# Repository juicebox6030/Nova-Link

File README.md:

# NOVA-LINK

NOVA-LINK is an open wireless protocol and firmware SDK for live event applications
such as lighting, audio control, and synchronization. The intended system uses an
ESP32-S3 plugin host and a TI CC1352R radio co-processor.

The repository currently provides a **portable C99 implementation of the protocol
and application core**, with tests and an in-memory simulation. Native SPI host
and slave adapters provide portable asynchronous ownership boundaries; physical
SPI/GPIO drivers and over-the-air operation still require implementation and
validation. Dual-band
redundancy and sub-5 ms delivery are design targets, not measured capabilities.

## Build and try it without hardware

Requires CMake 3.16+ and a C99 compiler. Python 3 enables inspection and RF-budget tests;
Doxygen enables API documentation. The library has no third-party dependencies.

```sh
cmake -S . -B build -DCMAKE_BUILD_TYPE=Debug
cmake --build build --parallel
ctest --test-dir build --output-on-failure
./build/nova-sim
./build/nova-plugin-sim
./build/nova-plugin-fault-sim
./build/nova-spi-pair-sim
./build/nova-spi-duplex-sim
./build/nova-config-manifest examples/plugins.ini
./build/nova-inspect frame 'AA 06 03 AF FE 00 AA FF'
./build/dmx_loopback
```

The simulation sends 300 counter messages through two plugin hosts, framed
transport, radio queues, and simulated RF delivery. Every message arrives twice,
as a model of redundant bands; exactly one copy reaches the receiving plugin.
The 8-bit sequence counter wraps during the run. Time is logical, so this does
not measure RF latency or physical throughput.

For memory and undefined-behavior checks on a toolchain with sanitizer runtimes:

```sh
cmake -S . -B build/sanitized -DCMAKE_BUILD_TYPE=Debug -DNOVA_ENABLE_SANITIZERS=ON
cmake --build build/sanitized --parallel
ctest --test-dir build/sanitized --output-on-failure
```

Build just the library for integration:

```sh
cmake -S . -B build/core -DNOVA_BUILD_TESTS=OFF -DNOVA_BUILD_TOOLS=OFF -DNOVA_BUILD_EXTENDED=OFF
cmake --build build/core
```

Use `add_subdirectory()` and link `NovaLink::nova_link`, or install the SDK with
`cmake --install build/core --prefix <sdk-directory>` and use
`find_package(NovaLink 0.1 CONFIG REQUIRED)`. See the
[development guide](docs/Development.md) for plugin and embedded integration.
The independent DMX library is installed as `NovaLink::nova_dmx`.
Link `NovaLink::nova_plugins` for the included counter, Multiverse-model,
radio-link transport, asynchronous native SPI backend, logger, configuration and
capture plugins, or select their individual targets.
The base initializes with `nl_host_init_plugins()`; an unordered manifest starts
providers before consumers, and `nl_host_poll()` polls input then ticks plugins.
See [the compiled plugin guide](plugins/README.md) for the common module API.

Generate a standalone plugin starter with
`python3 tools/new_plugin.py my-plugin --kind application --output build/my_plugin`.
The generated CMake project uses the installed SDK and includes a lifecycle smoke
test and a reusable [plugin conformance suite](docs/Plugin_Conformance.md).
The [development guide](docs/Development.md) explains how to build it.
Link `NovaLink::nova_plugin_conformance` from plugin tests to check the common
lifecycle contract; reports distinguish exercised cases from unsupported optional
capabilities. `NovaLink::nova_fault_backend` provides selectable deterministic
delay, disconnect and congestion scenarios for transport tests. These developer
targets are separate from `NovaLink::nova_plugins` and the ESP-IDF component.
The [configuration service](docs/Plugin_Configuration.md) and offline
`nova-config-manifest` example compose installed plugins from bounded INI text.
Run `nova-plugin-fault-sim` for deterministic delayed transfers, disconnects,
congestion and explicit restart; see its
[scenario guide](docs/Transport_Fault_Simulation.md).
The [hardware preparation guide](docs/Hardware_Preparation.md) uses the documented
ESP32-S3, TI CC1352R and City Theatrical 5911 reference. Its capture service stages
raw observations in the existing JSONL schema; board I/O and real Multiverse RF
decoding still require implementation and measurements. Both documented vendor
compile projects build with pinned SDK/toolchain baselines; see the guide for
their artifacts and deployment records.
The [native SPI backend](docs/SPI_Backend.md) connects the radio-link provider to
a caller-supplied asynchronous driver. Its completion outcomes and receipt tokens
are local adapter metadata; the existing wire format defines no physical PUSH
acknowledgment or empty/error response.
`NovaLink::nova_spi_virtual` is an explicit developer dependency that connects
the actual host backend and slave helper using native serialized frames. Run
`nova-spi-pair-sim` for the counter/Multiverse-model pair under logical transfer
delays and injected faults. See the [SPI simulation guide](docs/SPI_Backend.md).
Run `nova-spi-duplex-sim` for simultaneous two-way 512-slot DMX using production
plugin ticks, exact frame checks, congestion, outage recovery and silence expiry.
The virtual driver is excluded from the production plugin aggregate and
ESP-IDF component; its software outcomes do not establish physical timing or
Multiverse interoperability.

## Implemented core

- Explicit DataFragment serialization, field/length validation, and golden vectors.
- Command framing and incremental parsing across arbitrary byte boundaries.
- Per-origin/per-zone duplicate and stale-packet rejection, including sequence wrap.
- Exclusive or shared read-only zone claims; globally accessible metadata zone 0.
- Static plugin registration with generation handles, startup rollback, shutdown,
  payload send/receive, periodic hooks, and guarded structured logging callbacks.
- Named modules with declarative claims, provider dependencies, transactional
  manifest startup, and dependency/ownership checks during shutdown.
- Lifecycle-managed transport and logging providers using the same plugin API.
- Configuration service with bounded, schema-validated INI buffers and typed values.
- Bounded TX/RX queues with in-process backpressure, retry-safe deduplication,
  and optional latest-state coalescing per stream.
- Clock-driven zone rounds, optional metadata slots, and bounded burst extensions.
- PUSH/PULL command handling with transactional PULL receipts, offline JSON
  inspection, an RF airtime calculator, and a counter plugin.
- Native complete-frame slave adapter and lifecycle-managed asynchronous SPI
  driver service, with immutable transfers and shutdown ownership checks.
- CMake installation, an ESP-IDF component definition, and Doxygen documentation.

All core storage is fixed or caller-owned. The library does not allocate memory,
create threads, read configuration files, or access a network or device. Its APIs
require serialized calls from the application's event loop. Zone checks provide
cooperative access control for trusted compiled plugins; they are not a memory
sandbox.

## Protocol

Eight logical zones are available: zone 0 for metadata, zones 1–7 for plugin data.
Plugins own application payload encoding. The implemented fragment is:

```text
[origin:3 | zone:3 | BURST:1 | MGMT_LISTEN:1][sequence:8][0..100 payload bytes]
```

The maximum serialized fragment is 102 bytes. Larger messages require an
application-defined fragmentation/reassembly format; the core returns an error
instead of truncating or inventing such a format.

The software transport envelope is `[0xAA][LEN][COMMAND][DATA]`, where `LEN`
includes the command. This makes the existing command list and variable payloads
unambiguous in software. Its compatibility with a future board adapter still
needs validation. The [protocol decisions](docs/Protocol_Decisions.md) explain
conflicting earlier notes, sequence limits, and unspecified commands.

## DMX and Multiverse work

The portable DMX library encodes level frames and parses validated UART
BREAK/MARK/byte events. The [Multiverse bench plan](docs/Multiverse_2_4GHz.md)
describes direct CC1352R interoperability work. The capture analyzer accepts
existing JSONL observations:

```sh
python3 tools/analyze_rf_capture.py examples/rf_capture.simulated.jsonl
```

The [Multiverse software emulator](docs/Multiverse_Emulator.md) now models both
TX and RX: chunked full/delta updates, asynchronous completion/retry ownership,
atomic receive reconstruction, duplicate/loss handling, and resynchronization.
Generate and replay a synthetic capture through the same C receive engine:

```sh
./build/nova-multiverse-sim --seed 42 --loss-percent 20 \
  --capture build/multiverse.synthetic.jsonl
python3 tools/replay_multiverse.py build/multiverse.synthetic.jsonl \
  --end-us 3130200 --summary-only
```

The installed `NovaLink::nova_multiverse` library exposes normalized DMX state
and adapter ownership APIs. Its synthetic test codec is excluded from SDK
installation. Actual Multiverse RF reception, decoding, transmission, and fixture
operation remain unimplemented and unverified; the RF format needs real evidence.
The analyzer also supports `--compare-stimuli baseline channel_1_32` to inspect
candidate byte differences in labeled captures without claiming channel decoding.

The installed `NovaLink::nova_multiverse_plugin` connects that engine to the
common host/module lifecycle. It segments a 512-channel frame into native NLM1
application payloads, retries queue pressure, and delivers complete RX frames
atomically. `nova-plugin-sim` runs it alongside counter, transport and logger
plugins with injected loss/corruption and final recovery. NLM1 is a documented
NOVA-LINK application format; real Multiverse RF still needs captures and hardware.

## Proposed compact hardware

The [DMX dongle and USB-C power barrel design](docs/hardware/DMX_Dongle_and_Power_Barrel.md)
describes a TI-only, fixture-adjacent isolated-DMX dongle requiring 2.4 GHz and
US 915 MHz RF hardware, with a 10–30 second
backup target, wired RDM/wireless management and DMX/RDM firmware-update provisions,
with USB-C power only, plus inline powerCON,
TRUE1 and NEMA 5-15 barrel variants with a rotating, positively locking USB-C
center section. It includes an [illustrated design](docs/hardware/dmx-hardware-concept.html)
and [candidate BOM](docs/hardware/dmx-hardware-bom.csv). The
[manufacturer review package](hardware/compact-dmx/README.md) includes editable
Rev B CAD/STEP comparison geometry, dimensioned drawings and a partial DMX schematic.
The Rev C prototype captures power/buffer/cutoff/service circuitry and 2 MiB SPI
staging flash with USB power only, plus source-backed MCU support and a dual-band
frontend with a dual-feed antenna prototype and manual termination assembled OFF.
Three separate captured projects pass KiCad ERC. All37 physical MCU/RF/DMX parts
have footprint assignments:36 source-backed and one provisional switch. Cold-cap startup,
antenna tuning/coupling, complete PCB design, mechanism details, fixture fit and qualification remain open;
this is not released build-to-print hardware.
The [fixture reference manifest](docs/hardware/fixture-reference-manifest.md)
records retrieved manufacturer CAD for four fixtures across ETC, CHAUVET and GLP,
with connector-clearance measurements and physical fit still to be verified.

## Extended protocol prototype

The [extended prototype](experimental/extended/README.md) preserves the separate
implementation with CRC-8 link frames, metadata discovery, segmentation, INI
configuration, Python codecs, and a multi-node RF simulator. The default build
tests it alongside the SDK; use `-DNOVA_BUILD_EXTENDED=OFF` to omit it.

Its `[AA][CMD][LEN][DATA][CRC8]` transport differs from the SDK's
`[AA][LEN][CMD][DATA]`. Both libraries export overlapping `nl_*` symbols and
must be used in separate programs. The extended API is not part of the installed
SDK. Neither transport is an established physical-radio interoperability format.

## Project layout

| Directory | Purpose |
|---|---|
| `include/nova_link/` | Public C API |
| `src/` | Portable protocol, host, and radio core |
| `plugins/` | Compiled application, transport, logger and configuration plugins |
| `support/` | Reusable plugin conformance harness for developer tests |
| `examples/` | Native and Multiverse-model simulations and DMX loopback |
| `tools/` | Plugin starters, offline inspection, RF budgets/capture comparisons, and synthetic replay |
| `tests/` | Unit, integration, CLI, and installed-SDK checks |
| `platform/` | Board integration contracts and ESP-IDF component |
| `config/` | CMake package configuration |
| `experimental/extended/` | Separate extended API, simulator, codecs, and vectors |
| `docs/` | Architecture, development guide, decisions, and roadmap |

Generate the public API reference with `cmake --build build --target docs` when
Doxygen is installed. Output is `build/api-docs/html/index.html`.
The `docs-extended` target generates the prototype reference in
`experimental/extended/build/doxygen/html/index.html`.

The CI workflow template is [config/ci.github-actions.yml](config/ci.github-actions.yml).
Copy it to `.github/workflows/ci.yml` to enable GitHub Actions; publishing that
path requires GitHub authentication with the `workflow` scope. Local build and
CTest checks do not require it.

The [development roadmap](docs/Development_Roadmap.md) separates completed software
from remaining protocol decisions and board work. The [validation record](docs/Validation.md)
documents software checks, Opus 5.5 High checkpoint reviews, and RF assumptions.

## License and credits

[GPL-3.0](LICENSE). Designed by [Brent Scoggins](https://github.com/Juicebox6030),
[Luminary Technology and Productions](https://LuminaryTechnology.productions).
AI-assisted development.

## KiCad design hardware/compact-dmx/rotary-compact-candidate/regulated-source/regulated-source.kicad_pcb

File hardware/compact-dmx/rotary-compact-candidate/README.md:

# Compact rotary collar — bounded Phase 0 disposition

**Stop: the unchanged IRM-10-5 → long FPC → TPS25810 source path does not establish4.75V at a1.5A receptacle.** A completeØ60–64 mechanism is therefore not claimed or exported. This is the authorized Phase0 infeasibility branch, not a replacement production design. Only this new folder changes; integrated25, baseline CAD/BOM/docs and cell-protection remain untouched.

Four actual primary PDFs were fetched and read: MeanWell IRM-10 specification2025-08-08; TI TPS25810 SLVSCR1C July2017; Minco2019 Flex Design Guide; AllFlex Minimum Bend Radius Considerations. Manufacturer electrical/dimensional pages were rendered and inspected. Existing exact GCT A6 drawing/A3 specification and USB-C R2.4 primary cache were read. `sources.json` records paths/URLs/hashes; no distributor evidence, supplier contact or new tooling.

## Decisive electrical screen

IRM-10-5 is a fixed5V/2A/10W module,45.7×25.4×21.5 nominal, each dimensional tolerance±0.5. Its±2.5% output tolerance already includes setup,line and load regulation: **4.875V minimum at25°C**. Do not subtract line/load twice, assume output adjustment, or turn the3W model into a1.5A supply. Maximum ripple is200mVpp; it is not quietly treated as zero or a guaranteed symmetric±100mV waveform. Temperature coefficient±0.03%/°C applies0–50°C; no full-temperature low-voltage bound beyond it is inferred. Source:IRM-10 pp2–3.

TPS25810 power-path resistance maxima are37mΩ at25°C,46mΩ to85°C,55mΩ to125°C, specified at3A; using those resistances at1.5A is a conservative engineering DC screen, not a new characterization claim. In1.5A mode CHG=high,CHG_HI=low; short-circuit threshold1.58–1.82A. ItsCC controller advertises current, **does not regulate low VBUS upward**. TI §9 explicitly requires4.75–5.5V at the receptacle. Source§6.5,§8 and§9. A captive-cable source's different load-line allowance in USB-C R2.4§4.8.1.2 cannot be applied to this receptacle.

`screen.py` evaluates0.8/1.0/1.1m and35/70µm copper at20/80°C, with two8mm traces. Copperρ20=1.75e−8Ωm andα=.00393/°C are engineering allocations; actual finished foil resistance must be guaranteed by the flex supplier. Corner assumes width7.8mm, copper−10%,20mΩ total board/solder/termination resistance, plus55mΩ controller. The termination allocation **excludes mated connector/cable contact resistance**, so the test is not pessimistically charging cable loss to the source pin.

All12 combinations miss4.75V. Even an optimistic1m/70µm/8mm at20°C, no copper thinning, **zero termination loss**, and25°C controller37mΩ yields **4.72575V**. The explicit hot/process model is in `screen.json`; flex heating and individual drops are listed. This is enough to reject a guarantee without relying on unspecified cold, ripple or module thermal behavior.

At125°C-controller resistance, only28.33mΩ remains for the entire flex loop even with zero termination loss. At1m/80°C/8mm, that requires **190.8µm actual copper**; with the20mΩ termination allocation it requires **648.8µm**. These are mathematical break-even values before ripple, not proposed dynamic-flex constructions. Increasing trace thickness until the equation passes is not a credible compact clockspring design.

GCT USB4125-GF-A provides3A collectiveVBUS component capability. Its initial40mΩ/contact and post-test50mΩ/contact specifications concern a mated connector; equal sharing across twoVBUS/twoGND contacts would add a40/50mΩ total loop respectively, but current sharing must be established and this loss was not required to prove the source failure. Temperature rise testing is component-specific, not complete barrel qualification.

### One bounded compensation direction, not silently implemented

Retain the stationary isolated10W module but add **local regulated5.10V±1% on the rotating side, before TPS25810**, so the regulator sees and corrects flex drop. This requires a new selected buck-boost/power-stage design; no part is invented, installed or captured here. With55mΩ controller plus20mΩ downstream paths, conditional port minimum is4.9365V, leaving186.5mV for ripple/transient/additional uncertainties. This stays within5.5V at no load under the assumed regulation, but overshoot and fault limits need actual component evidence.

At90% allocated efficiency and15mW auxiliary output, input power is8.517W. With the worst screened70µm/1.1m hot FPC and the module's conditional50°C low4.8375V, solve the constant-power input quadratic: **1.843A**, regulator input **4.622V**. This is below2A nominal rating but is not startup/short-circuit/thermal qualification. A part must demonstrate the required efficiency, input range, current limit, output regulation, soft-start and protection before this can be adopted. Thick copper, extra regulator footprint and heat all affect compactness; no complete64mm packing is claimed.

IRM-10's horizontal free-air curves give full power only through50°C and≥100VAC; output derates at higher temperature and below100VAC. It is75% around60°C, which cannot supply an8.517W regulator input.77% module efficiency is typical, not worst;8.517W at77% implies about2.54W module heat, plus converter/FPC/controller heat in the enclosure. A provisional design study could restrict module-local ambient to0–40°C and line≥100VAC, but **external barrel ambient and enclosed full-load performance remain undeclared/unqualified**. All three mains end families stay stationary with PE; their connector voltage/current/endcap/approval limits remain baseline gates. This direction does not authorize a source architecture change.

### Separate connector compliance objection

The exact GCT is six-contact/power-only: no D+/D− contacts. USB-C R2.4§4.8.1.1 requires a non-data receptacle charger to advertise≥1.5A and short D+/D− below200Ω for legacy charging compatibility. TPS25810+this connector cannot implement that physical connection. This does not negate the connector's current rating or the sidecar sink candidate, but **a compliant general charger claim is unsupported**. Parent must resolve product/connector requirements before source release; no alternative family search is performed.

## Mechanical feasibility boundaries — not a motion validation

Baseline remains stationaryØ48×142,Ø84×26 collar,Ø64 index ring, approximatelyØ80 source-board allocation. Mains, PE and AC/DC module do not rotate. A64mm outer shell with1.5mm wall permits outer dynamic radius30.5; allow inner dynamic radius25 for core/bearing/barrier clearance. Proposed study construction:20mm axial width, single RA copper layer, two8mm traces separated1mm and1.5mm edge margins. A0.16mm **allocated** total flex thickness is not a supplier-approved70µm stack. No plated features/stiffener ends in the active bend; tangential clamped terminations and independent axial faces are mandatory. Minco calls for single-layer dynamic flex and avoiding plated bend conductors; neither guide certifies our bend cycle life. AllFlex static thickness-ratio examples are not promoted to dynamic endurance ratings.

A simple six-turn Archimedean spiral at radii25..30.5 has **1046.165mm** neutral length and0.9167mm pitch. `spiral-diagnostic.csv` samples181angles,−90..+90, with finite0.16mm thickness: radial interturn gap stays≥0.72mm. **But its length changes−43.589/+43.589mm** when turn count changes±0.25 with both radii fixed. It is not an inextensible cable solution, and its end tangent also changes. If length is instead held constant by letting the outer radius move, the−90° state needs **R32.912mm**, already outside the30.5mm dynamic boundary; it also breaks the fixed rotating termination radius. This falsifies that tempting procedural shortcut, **not every possible elastic clockspring**.

Accordingly no181-position collision PASS, constant-length mechanism, working hard stops or shrink STEP is fabricated. A true candidate needs an inextensible elastic strip/path model with both tangent clamps, contact/friction/finite pitch and guides, then supplier validation. Arbitrary wire torsion is rejected; no twist-life source supports it.

Axial-end USB is better than the old radialØ80 envelope, but not yet a complete pack. For example, place a1mm board with inner faceR26, topR27. GCT nominal3.16height and8.94tangential width gives outer corner radius `sqrt(30.16²+4.47²)=30.489mm`. With source drawing general±.25, use3.41height/9.19width: **R30.755mm**. Add1.25mm wall plus0.25 pose/process reserve → **OD64.51mm**, before plug opening, controller/capacitors, flex terminations or lock. Lowering board radius0.25 would approach64mm but consumes inner bearing/barrier space and needs actual footprints.Ø54 is not credible here;Ø60 is only a cassette investigation, not complete USB/lock hardware. The6.8±.15 axial connector length, finite stakes, controller/capacitors and strain relief need their own axial bay.20mm FPC+cheeks/bearings+endface electronics/lock will exceed old26mm collar width; a wider central bay might remain inside142mm core but has not been packed. No exact assembly envelope is asserted.

A separated end-face index ring is plausible geometrically:13holesØ2.2 atR28/15° have about5.11mm ligament between adjacent holes. A2mm pin with1.5mm steel ring at an **engineering1Nm abuse target** sees35.7N tangential force,11.37MPa single-shear nominal stress and11.90MPa bearing stress. These are load/stress calculations only: material allowables, fatigue, pin support, bending/engagement, ring fasteners and positive release stroke are not designed or rated. Stops must remain independent of the index pin and outside the flex bay; a missing stop track or passage cannot be excused by static stress numbers. No lock-bypass/pinch or service-assembly PASS is claimed.

## Deliverables and stop condition

`screen.py`, `screen.json`,181-row `spiral-diagnostic.csv`, `phase0-summary.pdf`, source assets/ledger, frozen input hashes and `receipt.json`. Run `python3 hardware/compact-dmx/rotary-compact-candidate/screen.py` to reproduce calculations. **No FreeCAD/STEP was generated:** the requested Phase0 check failed before detailed design, and exporting a shrink shell would falsely imply closure. Existing84mm CAD remains unchanged. The next justified work is selecting/qualifying the local voltage-compensation stage and resolving the source connector, followed by one constant-length spiral/termination and complete end-face packaging design. No owner approval is requested here; parent can integrate this concrete disposition.

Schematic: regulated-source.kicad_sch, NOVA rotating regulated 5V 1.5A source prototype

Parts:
C1, C2, C9: GRM21BC71E106ME11L 10uF; C0805
C3, C7: TMK107BBJ106MA-T 10uF; C0603
C4, C5, C6: GRM21BC81C226ME44L 22uF; C0805
C8: T520D157M010ATE055 150uF; T520D
C10, C11, C13: TMK105B7104MV-FR 100nF; C0402
C12: GRM155R71E103KA01D 10nF; C0402
D1: TPD1E10B06DPYR; DPY2
J0: FABRICATED_FPC20_SOLDER_LANDS; FPC20
J1: USB4105-GF-A; USB4105
L1: XFL4020-152MEC 1.5uH; XFL4020
R1: TNPW040224K9BYED 24900ohm; R0402
R2, R4, R7: TNPW040210K0BYED 10000ohm; R0402
R3: TNPW040237K4BYED 37400ohm; R0402
R5: TNPW04021K00BYED 1000ohm; R0402
R6: TNPW040254K2BYED 54200ohm; R0402
R8, R9, R10, R11: TNPW0402100KBYED 100000ohm; R0402
TP1: FAB_FAULT_PROBE; TP1
U1: TPS259474LRPWR; RPW10
U2: TPS63070RNMR; RNM15
U3: TPS25810RVCR; RVC20

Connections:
FPC_5V: C13.1, J0.1 (STATIONARY_IRM20_PLUS_VIA_FPC), R1.1, R3.1, U1.5 (IN)
GND_ISO: C1.2, C2.2, C3.2, C4.2, C5.2, C6.2, C7.2, C8.2, C9.2, C10.2, C11.2, C12.2, C13.2, D1.2, J0.2 (ISOLATED_RETURN_VIA_FPC), J1.A1_B12 (GND_shared_land), J1.B1_A12 (GND_shared_land), J1.S1 (SHELL), J1.S2 (SHELL), J1.S3 (SHELL), J1.S4 (SHELL), R2.2, R4.2, R5.2, R7.2, R9.2, U1.4 (PGTH_UNUSED), U1.8 (GND), U2.1 (PS_SYNC_LOW_FORCED_PWM), U2.4 (GND), U2.10 (PGND), U2.15 (VSEL_LOW), U3.8 (CHG_HI_LOW), U3.12 (GND), U3.21 (EP_GND)
INPUT_DVDT: C12.1, U1.7 (DVDT)
INPUT_ILM: R5.1, U1.9 (ILM)
INPUT_OVLO: R3.2, R4.1, U1.2 (OVLO)
INPUT_UVLO: R1.2, R2.1, U1.1 (EN_UVLO)
PORT_FAULT_OD: R11.2, TP1.1, U3.1 (FAULT_N)
PROTECTED_IN: C1.1, C2.1, C3.1, U1.6 (OUT), U2.12 (VIN), U2.13 (VIN), U2.14 (EN)
REF: R10.1, U3.10 (REF)
REF_RTN: R10.2, U3.9 (REF_RTN)
REG_5V136: C4.1, C5.1, C6.1, C7.1, C8.1, C10.1, R6.1, R8.1, R11.1, U2.7 (VOUT), U2.8 (VOUT), U3.2 (IN1), U3.3 (IN1), U3.4 (IN2), U3.5 (AUX), U3.7 (CHG_HIGH)
REG_FB: R6.2, R7.1, U2.5 (FB)
REG_READY_OD: R8.2, R9.1, U2.2 (PG), U3.6 (EN)
REG_VAUX: C11.1, U2.3 (VAUX_NO_EXTERNAL_LOAD)
SW_L1: L1.1, U2.11 (L1)
SW_L2: L1.2, U2.9 (L2)
USB_CC1: J1.A5 (CC1), U3.11 (CC1)
USB_CC2: J1.B5 (CC2), U3.13 (CC2)
USB_D_SHORT: J1.A6 (D_PLUS), J1.A7 (D_MINUS), J1.B6 (D_PLUS), J1.B7 (D_MINUS)
USB_VBUS: C9.1, D1.1, J1.A4_B9 (VBUS_shared_land), J1.B4_A9 (VBUS_shared_land), U3.14 (OUT), U3.15 (OUT)

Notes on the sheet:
PROTOTYPE: stationaryIRM20-5/FPC input only. No mains/PE or module circuitry captured here. All physical source board parts shown.
U1 reverse-blocking input, UVLO/OVLO and latched circuit-breaker. U2 forcedPWM5.136V, PG enables U3 after unloaded startup; no firmware.
U3 CHG=REG5V, CHG_HI=GND:1.5A only. CC1/CC2 independent. No USBdata processing or PD voltage escalation.
J1 has16 contacts but12 shared signal lands +4shell stakes, per originalGCTB4. D+ and D- tied by copper; no invented separate ground/VBUS pads.
Bulk150uF+76uFceramic before cold socket switch. ESR/capacitance attemperature, startup/inrush/thermal/ripple/faults remain physical gates.
Shell tiedisolatedGND proposal. No rotatingPE; accessiblemetal bonding/mainsendcap/harness/safety remain parent scope.
Connector height3.31+/-0.15mm EXCEEDS3.2mm target. Placement is unrouted; no collar fit, USBcompliance or manufacturingrelease claim.

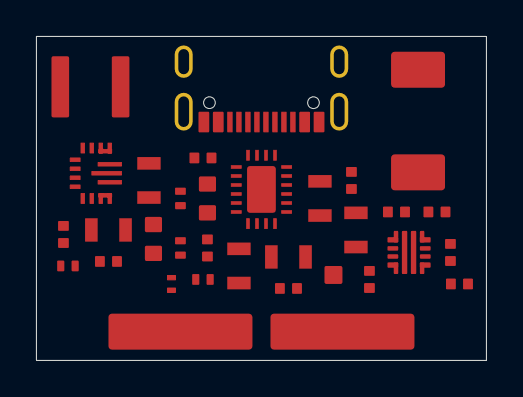
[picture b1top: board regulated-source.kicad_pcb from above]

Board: 2 copper layers, 25.0 x 18.0 mm, 32 parts (0 on the bottom side), 20 nets, no tracks yet.

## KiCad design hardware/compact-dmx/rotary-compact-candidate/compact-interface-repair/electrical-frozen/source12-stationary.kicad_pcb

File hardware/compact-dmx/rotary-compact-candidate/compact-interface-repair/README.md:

# Compact interface repair — mechanical prototype

This candidate changes only this directory. The frozen electrical boards are copied byte for byte; they remain **unrouted and electrically unqualified**. Mechanical validation does not establish source protection, USB compliance, thermal capacity, dynamic-flex life, mains construction or a released product envelope. The parent repair brief is a parent engineering instruction, not an owner-verbatim correction.

The primary branch repair uses explicit swept Ø3 mm conductor envelopes and four Ø2 mm passages through the copied carrier. Source pins remain nominal Ø1 mm; a separate Ø1.5 mm screen leaves 0.25 mm radial passage clearance. This is not an approved pin tolerance, solder land, insulation system or retained carrier. Source installation reservations remain 10 mm around/above and 5 mm below maximum pin projection, plus the existing film allocation. Electrical lead crossings of that reservation are expressly unqualified construction interfaces.

## Actual S12 geometry and mechanical changes

`electrical-frozen/` contains the two unchanged S12 boards and the actual exported netlist. `actual-boards.json` is extracted with KiCad from those frozen originals: 45 rotating and 12 stationary footprints, 189 numbered pads. It retains actual pad identifiers, shared-pad features, drill/land dimensions, layers, nets, values and footprint IDs. Component solids are S12's saved **body/height allocations**, not invented supplier 3D profiles. The native document contains 360 single-solid CAD objects, including named reserves, alternate ribbon poses and individual lands; this is not a count of manufactured parts. The native assembly includes each physical land; the assembly STEP omits copper detail, supplied separately by the native model and land-detail export.

Both transforms are proper rotations (−90° about X, determinant +1):

| Board | Local to assembly coordinates, mm | Result |
|---|---|---|
| Stationary 24×16×1 | X=22.2+x; Y=14.5+z; Z=8−y | Inside the Ø43 core bore; original component and land positions unchanged |
| Rotating 32×26×1 | X=52.2+x; Y=26.1+z; Z=13−y | PCB ends X84.2; maximum USB body ends X86.37, **not a mating plane** |

The rotating shell trial is Ø70: inner radius33.75, outer35. The larger S12 board/clamp drives it; it is not a global minimum. The core allocation is Ø48×87 rather than preserving unused142 mm length. The sourcepod and two24 mm connector blanks remain counted comparison allocations. A removable axial end gate allows board insertion on edge rails before the gate is installed. Three integral edge retainers avoid new holes in the unchanged PCB. Two M1 gate screws engage proposed pilot bosses outside the board and copper. The board has0.3 mm nominal axial and0.25 mm lateral side clearance; upper clips have0.35 mm nominal vertical play. With an **engineering allocation**, not a supplier grant, of board length/width/thickness±0.1 and each support datum±0.05, minimum axial clearance is0.1, lateral clearance0.15 each side, and vertical clearance0.15 mm. Plug-force transfer, connector solder/stakes, clip creep and allowable play remain physical gates.

The stop peg remains Ø2 atR28.5 with the same track and±90° tangency. Its axial extension is1.3 mm, with a new13 mm axial return bridge and a radial leg outside the developed fanout. Bridge-to-track axial separation is0.3 mm nominal; allocating±0.1 at both faces leaves0.1 mm. The bridge passes around the ribbon edge rather than cutting through its travel. The original13-position index mechanism, captive spring-return pin and independent stop remain distinct. No holding-torque rating is assigned.

For an illustrative0.5 N·m stop load: tangential force17.54 N, Ø2 peg average single-shear stress5.58 MPa. A13 mm cantilever with3×5 mm section has nominal bending stress18.25 MPa for the indicated load direction (I=31.25 mm⁴). This ignores stress concentrations, impact, joint flexibility and creep. PEEK structure/shoes, acetal bearing surfaces and stainless screws/pin remain engineering material choices without approved allowables.

## Finite stationary and moving connections

The stationary board receives the module leads at its **actual J0 lands**, not at a disconnected flex-tail box. Each source lead has a modeled copper-equivalent Ø1 mm conductor, Ø2 mm insulation envelope, finite curves/turns and a bare terminal region. A retained two-piece guide beyond PCB edge Z8 captures the insulated straight sections; its upper half is integral with the existing axial-screw corner cap. Nominal channel contact is not a qualified pull-strength or insulation-compression specification. The last local correction smooths the terminal turns: minimum proposed centreline radii are 2.347 mm positive and 1.979 mm return. The earlier 0.629 mm positive turn was rejected because it was tighter than the allocated insulation radius. `wire-radius-check.json` checks 1,342 replacement-wire pairs, confirms the other 356 native parts unchanged within the documented save tolerance, and preserves the certified R24 motion bound. Both source-pin endpoints have explicitly bounded copper overlaps below 0.089 mm³; these are proposed solder junctions, not qualified terminations. These remain tight **engineering static bends**, not supplier-approved wire limits; a selected wire may require more space. Wire family, insulation OD/tolerance, current/temperature, source-pin soldering and unprotected module-to-U1 segment remain construction gates.

The fixed static flex extension is a ruled, developable20 mm-wide strip with two8 mm copper lanes and1 mm separation. It enters a bounded copied core/spool passage and terminates on the actual J2 pads. A removable bridge shoe captures the straight section, supported by the core; axial M1 screws avoid the active winding and PCB. A second developed strip connects the original moving tail to actual J3. Its removable shoe has outboard screw ears and dedicated driver passages outside the ribbon. At the moving terminal, the saddle ends at Y26.24, the 0.16 mm ribbon occupies Y26.24..26.40, and the shoe starts at Y26.40. Local shoe pockets and head/shaft passages remove the previously found support overlaps; screw pilot engagement is 0.74 mm. Neither static extension is counted as part of the1046.167655992167 mm active winding.

The proposed single-layer stack is70 µm rolled-annealed copper within0.16 mm total thickness, copper offsets−0.055..+0.015 mm. The two dielectric faces are25/65 µm allocations. Both faces of the **static** solder windows are open; there are no holes or plated features in the active bend. Explicit0.13 mm solder preforms connect exposed copper to the nominal35 µm PCB lands. The fixed end uses opposite-side access to the same copper layer, preserving positive/return lane order without crossover. Minco's retrieved guide lists one-layer/two-sided-access construction (p10); it does not approve this stack, forming, solder process or duty cycle. Its bend-radius discussion describes10× thickness as an indicator, not a qualification. `fanout-probe.json` and `moving-path.json` retain the actual proposed paths; the supplier must approve their static shapes, tolerances and retention. No passive elastic equilibrium or endurance is inferred from CAD.

The contact graph distinguishes physical copper/solder contacts from the **schematic-only, unrouted** path through U1 between J0 and J2. Thus this is not an electrically continuous finished source assembly. FPC positive is J2.1→fixed lane1→active lane1→moving lane1→J3.1; return is the corresponding lane2/GND_ISO. No mains or PE rotates.

## Assembly and access basis

1. Keep both stationary ends open. Install the copied spool/core interfaces and feed the20 mm static flex terminal through its bounded passage before winding/closing the rotor. The enlarged original static tail and stiffeners stay outside; no lead passes through solid adhesive.
2. Slide the stationary PCB axially into its edge seats. Solder J0 and J2 using the defined axial tool approach. The bridge retainer can be translated with2 mm radial lift inside the bore before lowering to its nominal seat; this sequence still needs physical assembly/fixture confirmation. Fit the axial M1 cap screws from the open core ends. Sourcepod/endcap attachment must not precede this access.
3. Slide the rotating PCB from +X onto its rails, with rear gate and loose fanout shoe absent. Fit the gate and two external M1 screws. Attach J3 using the axial solder-tool passage, then capture the static tail. Dedicated radial driver holes reach the two clamp screws outside the ribbon edge. These are engineering tool envelopes, not a guarantee for every driver/iron.
4. Close the rotor around the unchanged active winding and fixed spool, retaining the original frame-screw, pin, spring and cap assembly sequence. Verify actual return, all13 engagements and independent stops physically before any use.

No foam covers component tops and no conductive heatsink contacts unspecified pads. Thermal airspace is only geometric allocation; no sealed-collar heat path or temperature qualification follows.

## Connector and envelope limits

The24 mm blanks are **comparison geometry only**. CI-R1 nominal rear-depth corrections, before terminals/wire/tools, are:

| Variant | Additional axial depth over two24 mm blanks |
|---|---:|
| NAC3MPXXA/B classic | 6.4+6.4 =12.8 mm |
| NAC3MPX-TOP / NAC3FPX-TOP | 7.2+8.8 =16.0 mm |
| Leviton5278-C /5279-C | 21.3+19.6 =40.9 mm; Ø63.5 flanges also required |

These are lower-bound **deltas**, not completed end assemblies or an accepted total product length. CME-R1 has zero accepted installed mating transforms. Standalone FXX79–82.5 and TRUE1 77–80 mm lengths are not installed cable projections. Panel shoulders are not mating planes. Latch/hand sweeps, terminal/sleeve/tool profiles, model revisions and approved NEMA cords remain unknown; no guessed mated parts were added. Classic gray/B needs the specified B-to-A jumper to a fixture A inlet, never direct B-to-A mating.

The finite12×6.5×12 plug,18 mm relief andØ6×80 cable are engineering screens only. Exact USB plug body/mating datum and cable bend qualification remain open, as does every fixture fit. In particular, the wider NEMA flange may obstruct the USB cable screen; the Ø48 blank cannot establish clearance for it.

## Reproduction and acceptance

All writes stay here. The `before-*.FCStd` files are frozen proof snapshots, not alternative current assemblies. `check-local.py` intentionally rechecks the pre-seat snapshot; `check-repaired.py` composes the subtractive-seat proof against the pre-wire snapshot, and `check-wire-radius.py` then checks the final four replacement wires against the current native assembly. Development logs can contain superseded failed trials; only the named JSON checks and receipt constitute final acceptance evidence. Run `extract.py` with existing Flatpak KiCad10.0.7; run CAD scripts through `run.py` with `QT_QPA_PLATFORM=offscreen` and `ALLOCATION_SCRIPT=<script>`. `build.py` reproduces the native model from frozen sources. The final seat repair is purely subtractive: two rear driver counterbores, a wire-guide seat, moving-shoe/head/shaft passages, an end-gate face trim and full-depth pilot passages. `check-repaired.py` proves both changed solids are subsets of the pre-repair parts; every other cleaned BRep retains its topology and numeric tokens within 1e-12 save-normalization tolerance. This preserves prior zero intersections; all previous positive pairs involving those two supports are recomputed. Independent checks cover actual pad centroid/area/net contracts, full physical overlap records, source reservations, contacts, motion/stops/locks, tool and insertion paths, saved-solid validity and STEP reopen. `receipt.json` is the authoritative result: **a native-valid solid alone is not a geometry PASS**.

Unmet regardless of geometric outcome: retained/insulated source carrier and mains construction, variant endcaps/mates, S12 routing/protection/startup/thermal/current/fault behavior, supplier package profiles, flex stack/forming/endurance, wire/termination process, material/fastener/bond allowables, assembly and physical tolerances, EMC/USB/product safety certification, and compactness/fixture acceptance.

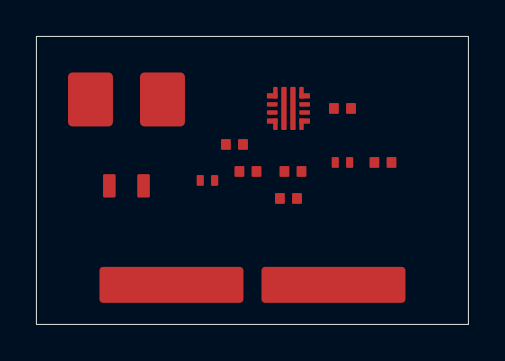
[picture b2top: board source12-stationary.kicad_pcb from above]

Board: 4 copper layers, 24.0 x 16.0 mm, 12 parts (0 on the bottom side), 8 nets, no tracks yet.

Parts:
C1: MSAST21GBB5106MTNA01 10uF; C0805
C11: GRM155R71E103KA01D 10nF; C0402
C14: TMK105B7104MV-FR 100nF; C0402
J0: FAB_SOURCE12_WIRE_LANDS; Wire2
J2: FAB_FPC20_STATIONARY; FPC20
R1: TNPW040268K1BYED 68100ohm; R0402
R2: TNPW040210K0BYED 10000ohm; R0402
R3: TNPW0402100KBYED 100000ohm; R0402
R4: TNPW04029K09BYED 9090ohm; R0402
R5: TNPW04022K00BYED 2000ohm; R0402
R6: TNPW0402100RBYED 100ohm; R0402
U1: TPS259474LRPWR; RPW10

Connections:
FPC12_PROTECTED: J2.1, U1.6
GND_ISO: C1.2, C11.2, C14.2, J0.2, J2.2, R2.2, R4.2, R5.2, U1.4, U1.8
MODULE12_UNPROTECTED: C1.1, C14.1, J0.1, R1.1, R3.1, U1.5
SOURCE_DVDT: R6.1, U1.7
SOURCE_DVDT_C: C11.1, R6.2
SOURCE_ILM: R5.1, U1.9
SOURCE_OVLO: R3.2, R4.1, U1.2
SOURCE_UVLO: R1.2, R2.1, U1.1

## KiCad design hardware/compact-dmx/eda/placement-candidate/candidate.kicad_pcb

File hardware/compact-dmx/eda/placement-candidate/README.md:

# Partial placement candidate — not a manufacturing board

One placement of the current 37 physical MCU/RF/DMX parts on the unchanged 90 × 28 × 1 mm PCB. Coordinates are the CAD coordinates directly: x4–94, y23–51; component side corresponds to CAD z11. Four Ø2.2 NPTH holes are at (7,26), (73,26), (7,48), (73,48). No baseline files were edited.

`candidate.kicad_pcb` embeds the actual editable library footprints. `generate.py` imports the two actual KiCad XML exports, rather than reconstructing nets from prose. `inputs.json` freezes source hashes, positions, assignments and statuses. `verify.py` independently reads the source XML again and checks all 156 numbered pads. DMX_TX/RX/RE_N aliases merge only their corresponding MCU nets. DMX_DE_SAFE and DMX_POWER_EN remain separate from MCU requests: the omitted power gating circuitry must connect them. All 67 imported nets are partial; they are not a complete product netlist.

Actual KiCad 10.0.7 DRC: **zero geometric violations, 89 unconnected items**. There are zero tracks, zero vias and no ground pours. This is not a clean manufacturing DRC result. Default KiCad clearance constraints are merely placement screening, not selected fabrication or isolation rules. Courtyard AABBs additionally pass the independent board-edge/cap/USB reserve check. No exclusions were installed. Four mechanical footprints are additional to the 37 electrical components.

## Mechanical and routing disposition

- U5 is rotated 90° at (18,36). Its isolated pads face the top board edge; logic pads face downward. The drawn x4–26/y34.8–37.2 strip is a reserved routing corridor, **not a claimed creepage rating**. No copper crosses it because no copper is routed. Only the isolator bridges the two sides. Ground pour setbacks, copper/slot geometry, actual creepage and clearance remain PCB design work.
- Propose moving the DMX lead entry from (72,20) to **(10,20)**, with the isolated wire landing approached near (10,24). This keeps the wire on the isolated side instead of crossing the logic/RF region. These are proposed enclosure/entry coordinates, not a captured connector or CAD modification. Strain relief, hole spacing, landing pads and separation from the mounting screw at (7,26) must be designed; no wire landing footprint is claimed.
- S_TERM is at (18,26.6), rotated 180°, with actuator toward the y23 edge. Reserve a polymer tool-access path approximately x16.35–19.65 from y20 to the actuator, separate from the proposed cable entry. Its actual courtyard is checked; enclosure access and travel are not proven.
- **S_TERM remains provisional.** Parent recovered the official active product page and 498359-byte PDF, SHA256 `6a758d151b7eee7f8cd59594bd92cfec4c9b1470e0743094f185f19e7ac2a868`. The manufacturer mechanical-pad inner gap is 1.13 mm; the current footprint has 1.41 mm, a 0.28 mm discrepancy. This placement intentionally does not silently repair the library. NPTH-to-row vertical registration still needs verified correction. Signal pads and Ø0.9 NPTH spacing are not the disputed dimensions. Active lifecycle does not approve these lands.
- Capacitor/body/lead projection x26–61/y23.5–37 is kept free of component courtyards. The actual cap bottom is z12, only 1 mm above the nominal PCB top. No component height or assembly tolerance proof is inferred. USB x36.5–48.9/y45.1–51 is also free. Both rectangles are drawing-layer constraints enforced by the verifier, **not native copper keepout rules**.
- A101 center (91.6,37), −90°, leaves 0.6 mm outer-pad copper-to-board-edge clearance. Its embedded provisional antenna keepout transforms to x83.4–93.4/y23–51. Preserve the additional empty strip to x94. Six NC lands retain distinct nets, with no ground connection. Matching components lie inward of the keepout; no other component is placed there.
- This antenna placement is a prototype interpretation, not the Johanson 30 mm reference board: actual width remains 28 mm. Fixture metal, housing, ground length/width, feed bends, tuning and port coupling require measurement. No claimed impedance or RF performance. Five RF tuning parts now use manufacturer-dimensioned Coilcraft/Murata lands; RF substitution/tuning remains unqualified. See ../footprints/REPLACEMENT-PASS.md.
- MCU and IPC are oriented toward each other but the balanced connections are **not routed** and the TI/Johanson reference geometry has not been reproduced. Direct balanced paths, RF feed crossings, crystal loops, decoupling vias and DC/DC current loops remain placement-refinement gates. Geometric fit does not establish acceptable electrical placement. No invented controlled-impedance stackup is embedded.

Power/buffer circuit, external SPI NOR, USB power connector, service/ROM/reset/cJTAG pads, cable landing pads and their decoupling/controls are **unplaced**. Empty space is not an allocation proof for them. No enclosure shrink, whole-product fit, fixture compatibility, assembly accessibility, RF qualification or release claim follows from this candidate.

## Reproduce locally

Run from the repository root, using the existing Flatpak installation:

```sh
flatpak run --command=python3 org.kicad.KiCad hardware/compact-dmx/eda/placement-candidate/generate.py
flatpak run --command=kicad-cli org.kicad.KiCad pcb drc --format json --severity-all -o hardware/compact-dmx/eda/placement-candidate/drc.json hardware/compact-dmx/eda/placement-candidate/candidate.kicad_pcb
flatpak run --command=python3 org.kicad.KiCad hardware/compact-dmx/eda/placement-candidate/verify.py
flatpak run --command=kicad-cli org.kicad.KiCad pcb export svg --layers F.Cu,F.Fab,F.CrtYd,Edge.Cuts,Dwgs.User --mode-single --page-size-mode 2 -o hardware/compact-dmx/eda/placement-candidate/placement.svg hardware/compact-dmx/eda/placement-candidate/candidate.kicad_pcb
flatpak run --command=kicad-cli org.kicad.KiCad pcb export pdf --layers F.Cu,F.Fab,F.CrtYd,Edge.Cuts,Dwgs.User --mode-single -o hardware/compact-dmx/eda/placement-candidate/placement.pdf hardware/compact-dmx/eda/placement-candidate/candidate.kicad_pcb
```

KiCad DRC without `--exit-code-violations` returns zero even with unconnected items; use the JSON counts, not its exit status, as evidence. `placement.svg` and `placement.pdf` show actual lands/courtyards and dimensioned coordinate annotations. `validation.json` retains measured courtyard bounds and input-mutation checks. The source footprints' manufacturer/reference provenance remains in the parent footprint ledger; no new package dimensions were invented here.

## Corrected candidate connectivity and partition

The initial candidate failed to normalize leading `/` in exported hierarchical labels, so its claimed TX/RX/RE aliases were not actually merged. The corrected generator strips leading slashes before applying the explicit aliases. Independent semantic assertions now require actual board U5.2=U1.19, U5.4=U1.18 and U5.5=U1.12, and retain separation between MCU requests and DE/power gates. Net count is 67; the three newly joined unrouted nets increase KiCad's unconnected count to 89.

The first placement also put termination resistors across/on the logic side of the drawn corridor. R_TERM1 and R_TERM2 are now at (6.5,32.2) and (9.2,32.2), both rotated 90°; C4 moves to (11.8,26.4). The verifier checks every non-U5 courtyard against the corridor and requires every part carrying isolated bus/supply/termination nets to remain wholly within x4–26 and above y34.8. C3, C4, both terminators and S_TERM pass. This is a geometric partition check, not a creepage certification. Source footprints, provisional switch status, omitted hardware and zero routing remain unchanged.

The PNG preview is cropped from the actual PDF at higher resolution with `pdftoppm -scale-to 4000 -x 0 -y 290 -W 1480 -H 540 -singlefile -png`; the SVG/PDF remain editable/vector placement exports.

## Stable export fingerprint correction

`inputs.json` retains raw export SHA256 values for provenance. Acceptance uses an additional parsed-XML fingerprint with **only top-level `design/date` text blanked**. All other parsed fields remain included, including values, MPNs, footprints, electrical pin types, nets and metadata. Source schematic and library footprint files remain raw-SHA checked. XML serialization normalizes parser formatting; it does not discard other XML elements/attributes. The generator establishes these fingerprints when producing the board, not during verification.

The verifier independently compares actual board values/footprint identities with the current exports and assignment contract, in addition to its existing pad/net semantics and spatial checks. In-memory regressions confirm a date change passes while value, footprint, net name, pin, pin type and other metadata mutations fail the fingerprint. No active source is mutated for these negative checks.

After generating this candidate once, both real netlists were exported again with KiCad10.0.7. The unchanged board passed verification with both raw export hashes different and both stable fingerprints equal. Parent subsequently ran the whole-package validator successfully, then verified the unchanged board again without regeneration or blind manifest refresh: both raw export hashes differed, all156 pads passed and no source mutations were reported. Board SHA256 `fe577602e2891b7c78ec8fba5d71f8648076cadccff2774c96e2673c6fb15a2b`; parent evidence `.tools/checks/revd-placement-parent/post-package-stable-receipt.json`. This closes the date-only false mutation failure. The CLI emitted an existing schematic annotation warning during export; exports completed and their electrical fingerprints remained identical. This pass does not claim that warning was repaired.

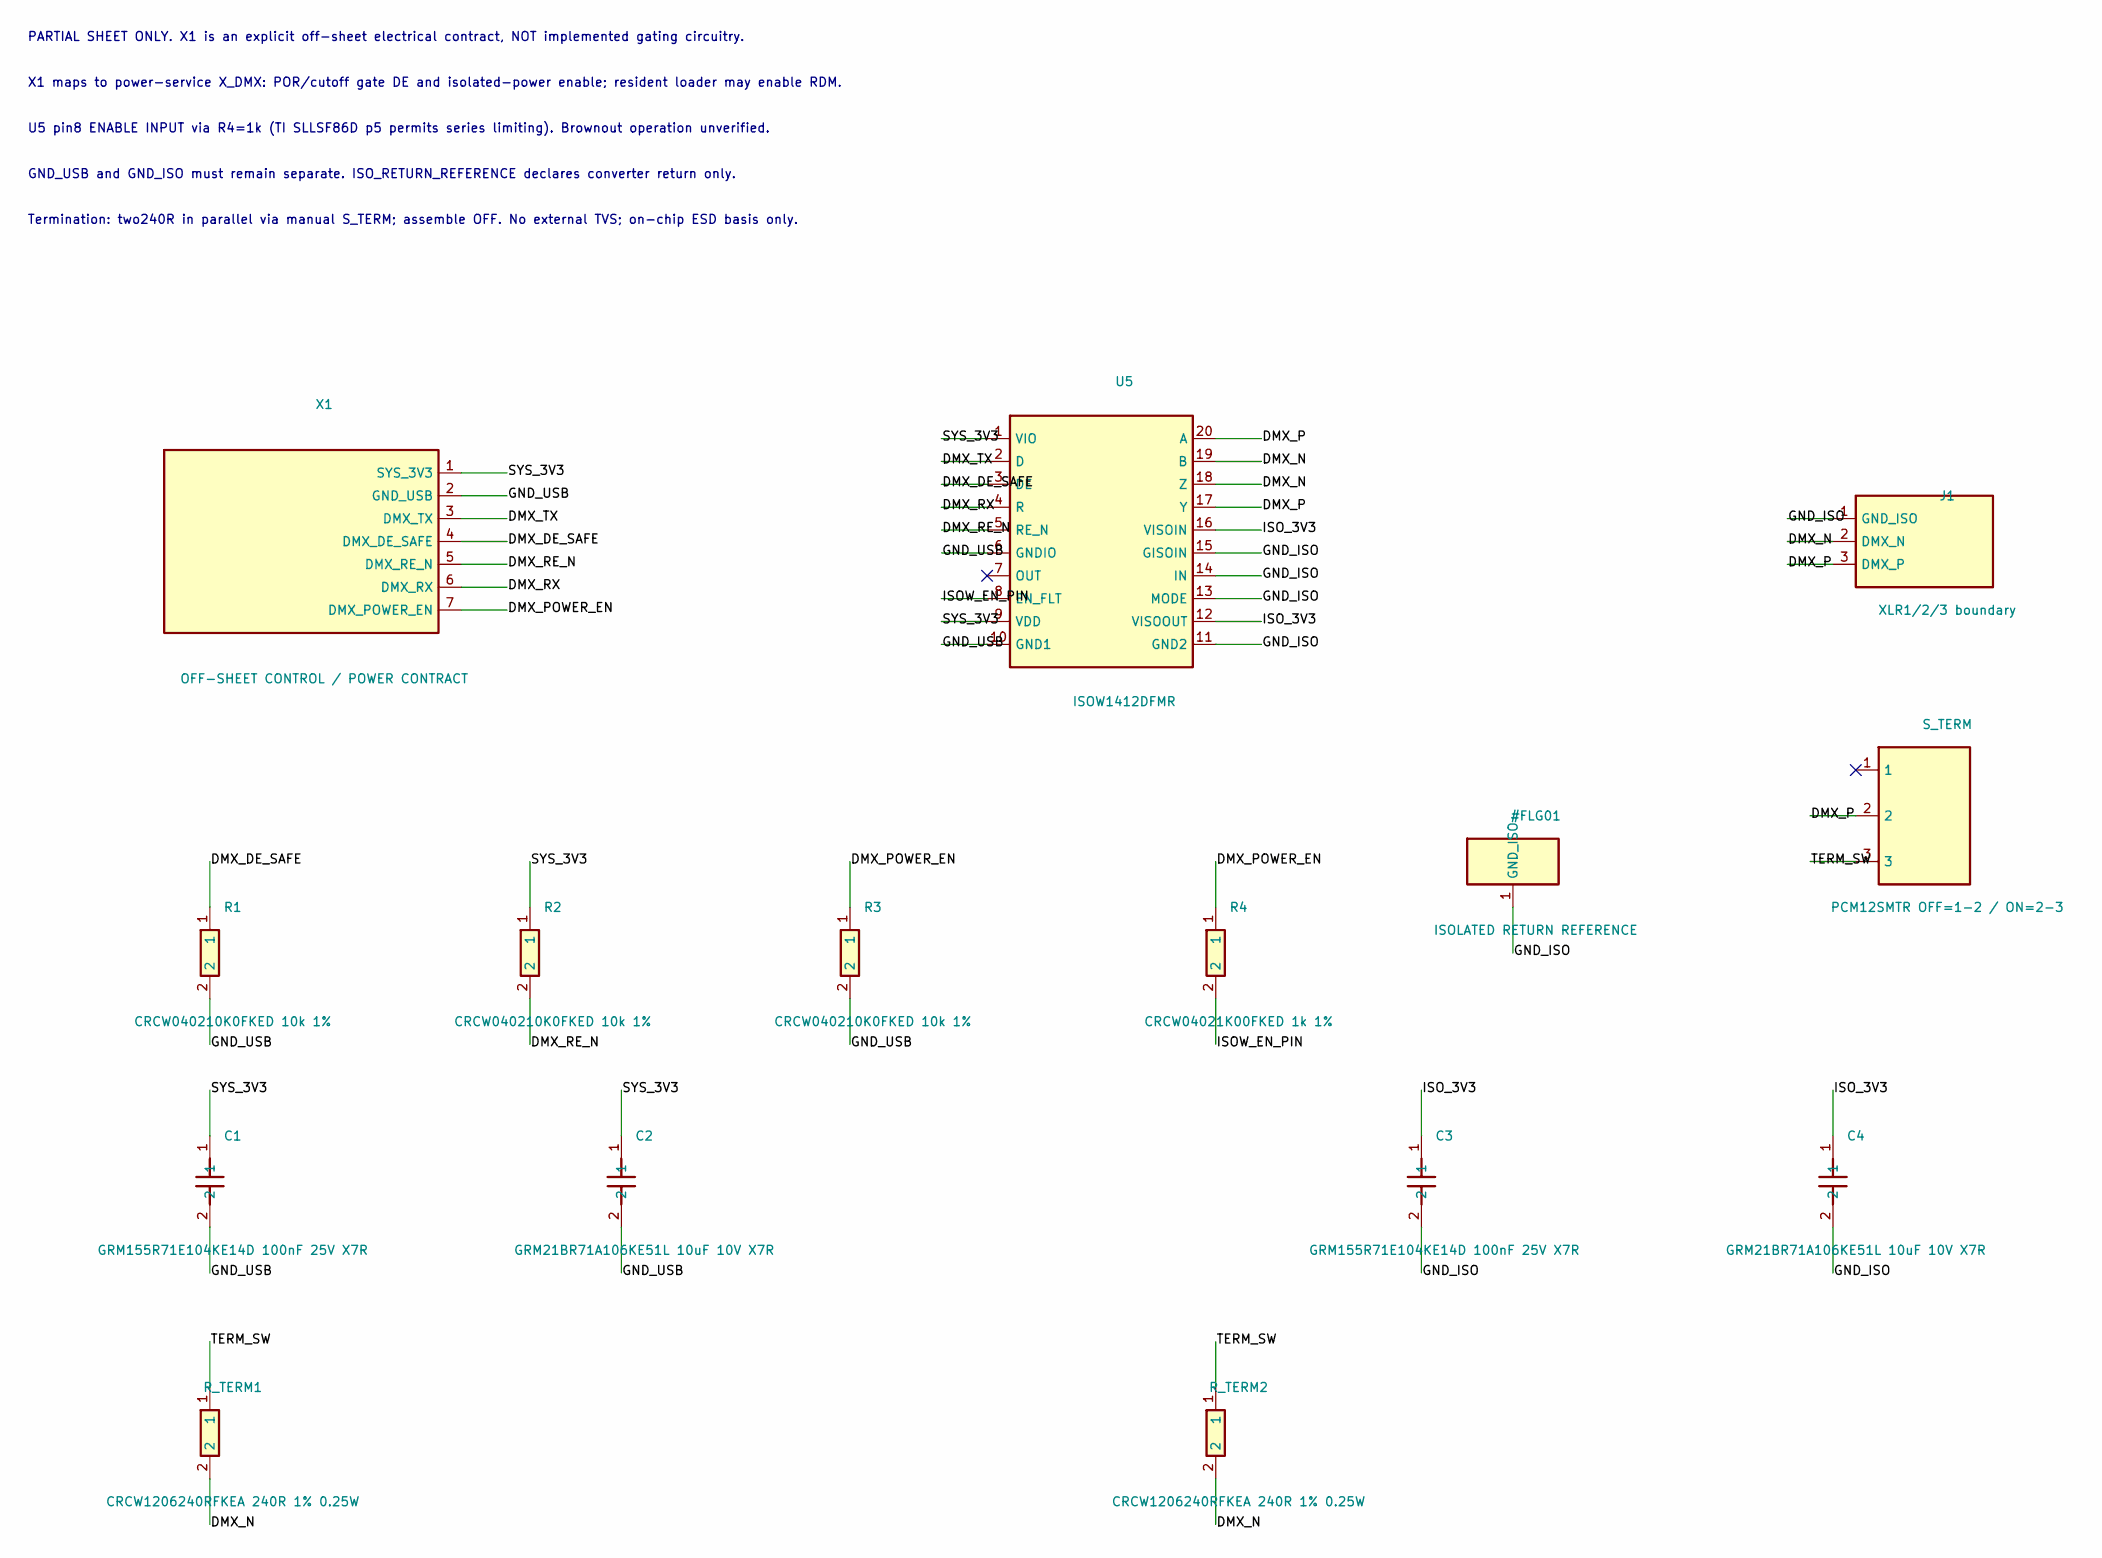
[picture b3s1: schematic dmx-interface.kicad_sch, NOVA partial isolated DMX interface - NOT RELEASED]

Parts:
C1, C3: GRM155R71E104KE14D 100nF 25V X7R; TI_CAPC1005_Vector
C2, C4: GRM21BR71A106KE51L 10uF 10V X7R; Murata_GRM21_Reflow
J1: XLR1/2/3 boundary
R1, R2, R3: CRCW040210K0FKED 10k 1%; Vishay_CRCW0402
R4: CRCW04021K00FKED 1k 1%; Vishay_CRCW0402
R_TERM1, R_TERM2: CRCW1206240RFKEA 240R 1% 0.25W; Vishay_CRCW1206
S_TERM: PCM12SMTR OFF=1-2 / ON=2-3; PCM12_PENDING_MANUFACTURER_LAND_RECHECK
U5: ISOW1412DFMR; TI_DFM0020A
X1: OFF-SHEET CONTROL / POWER CONTRACT

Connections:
DMX_DE_SAFE: R1.1, U5.3 (DE), X1.4 (DMX_DE_SAFE)
DMX_N: J1.2 (DMX_N), R_TERM1.2, R_TERM2.2, U5.18 (Z), U5.19 (B)
DMX_P: J1.3 (DMX_P), S_TERM.2, U5.17 (Y), U5.20 (A)
DMX_POWER_EN: R3.1, R4.1, X1.7 (DMX_POWER_EN)
GND_ISO: C3.2, C4.2, J1.1 (GND_ISO), U5.11 (GND2), U5.13 (MODE), U5.14 (IN), U5.15 (GISOIN)
GND_USB: C1.2, C2.2, R1.2, R3.2, U5.6 (GNDIO), U5.10 (GND1), X1.2 (GND_USB); also elsewhere on the board
ISOW_EN_PIN: R4.2, U5.8 (EN_FLT)
ISO_3V3: C3.1, C4.1, U5.12 (VISOOUT), U5.16 (VISOIN)
MCU_DMX_RX: U5.4 (R), X1.6 (DMX_RX); also elsewhere on the board
MCU_DMX_TX: U5.2 (D), X1.3 (DMX_TX); also elsewhere on the board
MCU_RE_N: R2.2, U5.5 (RE_N), X1.5 (DMX_RE_N); also elsewhere on the board
SYS_3V3: C1.1, C2.1, R2.1, U5.1 (VIO), U5.9 (VDD), X1.1 (SYS_3V3); also elsewhere on the board
TERM_SW: R_TERM1.1, R_TERM2.1, S_TERM.3
dmx_unconnected-(S_TERM-Pad1): S_TERM.1
dmx_unconnected-(U5-OUT-Pad7): U5.7 (OUT)

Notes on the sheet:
PARTIAL SHEET ONLY. X1 is an explicit off-sheet electrical contract, NOT implemented gating circuitry.
X1 maps to power-service X_DMX: POR/cutoff gate DE and isolated-power enable; resident loader may enable RDM.
U5 pin8 ENABLE INPUT via R4=1k (TI SLLSF86D p5 permits series limiting). Brownout operation unverified.
GND_USB and GND_ISO must remain separate. ISO_RETURN_REFERENCE declares converter return only.
Termination: two240R in parallel via manual S_TERM; assemble OFF. No external TVS; on-chip ESD basis only.
